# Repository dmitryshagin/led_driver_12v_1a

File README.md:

***WARNING! IT'S UNTESTED - I'VE NEVER BUILT THIS BOARD. But I will :)***

LED driver for powering Cree XHP35 LED at 1.05A from 3S LiPoly battery to use in underwater flashlight.

It's currently tuned up to work with 9-12.6V input.

Input can be easily changed to 4-25V with slight adjustment of R2 and R3. Increasing voltage over 25V is limited by used capacitors and FETs. You can change it upto ~60V with selecting new Q1-Q5, but PCB rework is also required.

Current is roughly set to 2A with R11, and is fine-tuned to 1.048A with R14&R15. Tuning R14 and R15 values makes it possible to set any current between 0-2A.

This driver is build around [LT3791](http://www.linear.com/product/LT3791)

I've also added Attiny24 to control PWM input and monitor input voltage. It can be ignored and never placed. Firmware will be added later, but the idea is to detect power loss with Q6, go to deep sleep and change working mode on power recovery. C16 gives uC ~4 seconds of life in power down mode, so we can switch power modes with one romote switch. Simulation gave me 10us for uC to go to deep sleep mode and it seems perfect.

You can download [gerbers](binaries/led_driver_12v_1a.zip?raw=true) to order this PCB from [SeedStudio](http://www.seeedstudio.com/service/index.php?r=pcb) - it's very cheap and has nice quality.

[BOM](https://www.digikey.com/classic/RegisteredUser/BOMBillOfMaterials.aspx?path=1&exist=1&id=3307608) - only for registered DigiKey users. Total cost is nearly $27 now.

Yo'll get something like this:

Board is 19.5x35mm and it should generate almost no heat - calculated efficiency is >96.5% and power loss is around 0.4W at 13W output.

It's also round version (32mm):

[Part List](part_list.txt?raw=true) is also included.

You can also take a look at LTSpice IV simulation and efficiency report. Schematic and PCB created with [Eagle 7.5](http://www.cadsoftusa.com/). It's not as nice and clean as I wanted it to be, but it should do the job.

**Changes required to use XHP70:**

It is very easy to modify this driver for XHP70 LED (12V version, at 2.4A). Modifications are simple:

* change R11 to 0.033 Ohm (sized 1206, power rating - 0.5 to 1W). Something like Panasonic ERJ-8BWFR033V. It will limit driver output current to 3A
* change R15 to 100k (0402 size) to fine-tune output current at 2.4A.
* change L1 to 10uH with sauration current at least 4A. Wurth Electronics 7447709100 will fit perfectly
* you can also remove L2 to boost efficiency to >98%, but it requires good wireing and low battery impedance (input current will pulse between 2.7 and 3.5Amps (with spikes to 10-15Amps) for 0.01 Ohm battery impedance). Instead we loose ~0.2W at L2, but have no power pulsation on input (<0.04A & stable input current 3.2A).

LTSpice simulation results:

* input power: 36.3W @ 11.7V
* output power: 35.5W @ 2.42A
* calculated efficiency: 97.8%
* LED current pulses: <1.7%

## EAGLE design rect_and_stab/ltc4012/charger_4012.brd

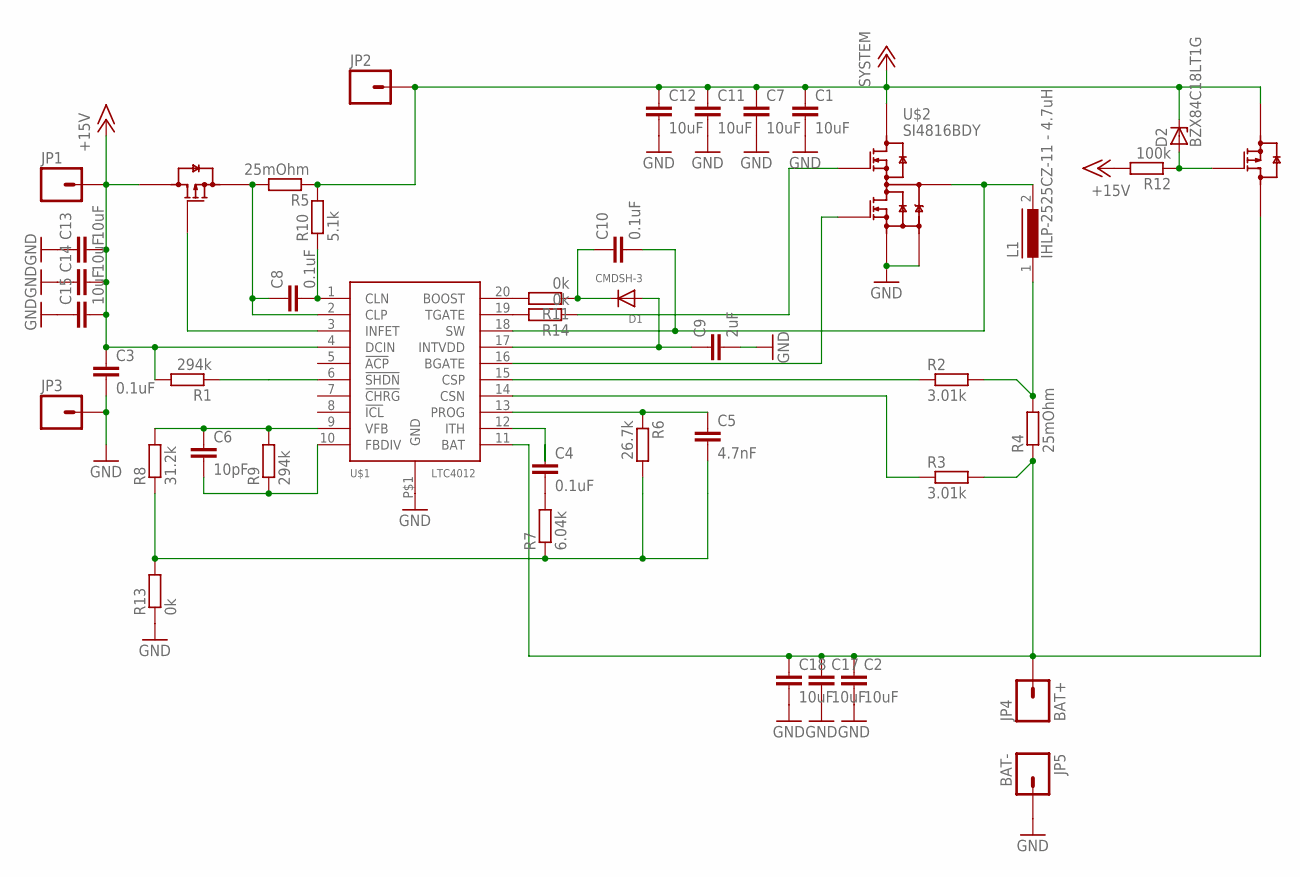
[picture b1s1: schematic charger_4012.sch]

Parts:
C1, C2, C7, C11, C12, C13, C14, C15, C17, C18: 10uF; C1206
C3, C4, C8, C10: 0.1uF; C0402
C5: 4.7nF; C0402
C6: 10pF; C0402
C9: 2uF; C0805
D1: CMDSH-3; SOD-323F
D2: BZX84C18LT1G; TO236
JP1, JP2, JP3: M01PTH_2MM; 1X01_2MM
JP4: BAT+; 1X01_2MM
JP5: BAT-; 1X01_2MM
L1: IHLP-2525CZ-11 - 4.7uH; DR73
R1, R9: 294k; R0402
R2, R3: 3.01k; R0402
R4, R5: 25mOhm; R2512
R6: 26.7k; R0402
R7: 6.04k; R0402
R8: 31.2k; R0402
R10: 5.1k; R0402
R11, R13, R14: 0k; R0402
R12: 100k; R0402
U$1: LTC4012; QFN20
U$2: SI4816BDY; SO-8
U$3, U$4: SI7423DN; POWERPACK1212

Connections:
+12V: C1.1, C7.1, C11.1, C12.1, D2.C, JP2.1, R5.1, R10.2, U$2.8 (D1), U$4.1 (S), U$4.2 (S), U$4.3 (S)
+15V: C3.1, C13.2, C14.2, C15.2, JP1.1, R1.2, R12.2, U$1.4 (DCIN), U$3.5 (D), U$3.6 (D), U$3.7 (D), U$3.8 (D), U$3.9 (D)
BAT: C2.1, C17.1, C18.1, JP4.1, R3.2, R4.1, U$1.11 (BAT), U$4.5 (D), U$4.6 (D), U$4.7 (D), U$4.8 (D), U$4.9 (D)
BGATE: U$1.16 (BGATE), U$2.4 (G2)
BOOST: C10.1, D1.C, R11.1
CLN: C8.2, R10.1, U$1.1 (CLN)
CSN: R3.1, U$1.14 (CSN)
CSP: R2.1, U$1.15 (CSP)
FBDIV: C6.2, R9.1, U$1.10 (FBDIV)
GND: C1.2, C2.2, C3.2, C7.2, C9.2, C11.2, C12.2, C13.1, C14.1, C15.1, C17.2, C18.2, JP3.1, JP5.1, R13.1, U$1.P$1 (GND), U$2.2 (A), U$2.3 (S2)
INFET: U$1.3 (INFET), U$3.4 (G)
INTVDD: C9.1, D1.A, U$1.17 (INTVDD)
ITH: C4.1, U$1.12 (ITH)
unnamed: R14.2, U$1.19 (TGATE)
unnamed: L1.1, R2.2, R4.2
unnamed: C4.2, R7.2
unnamed: R1.1, U$1.6 (!SHDN)
unnamed: C8.1, R5.2, U$1.2 (CLP), U$3.1 (S), U$3.2 (S), U$3.3 (S)
unnamed: R11.2, U$1.20 (BOOST)
unnamed: D2.A, R12.1, U$4.4 (G)
PROG: C5.1, R6.1, U$1.13 (PROG)
SGND: C5.2, R6.2, R7.1, R8.1, R13.2
SW: C10.2, L1.2, U$1.18 (SW), U$2.5 (S1/D2), U$2.6 (S1/D2), U$2.7 (S1/D2)
TGATE: R14.1, U$2.1 (G1)
VFB: C6.1, R8.2, R9.2, U$1.9 (VFB)

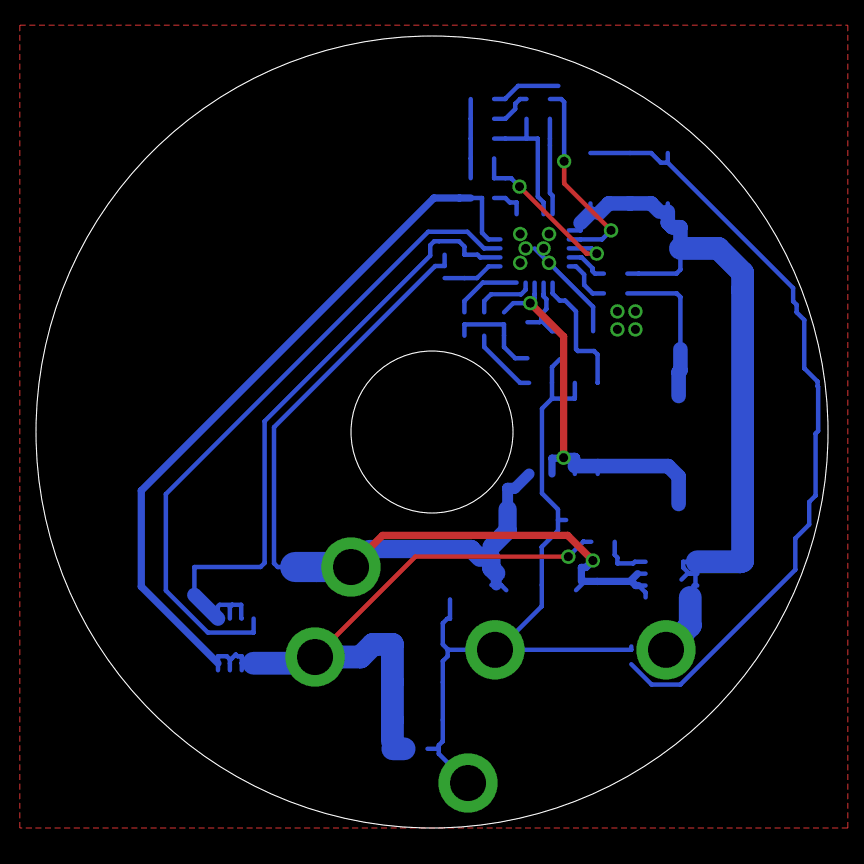
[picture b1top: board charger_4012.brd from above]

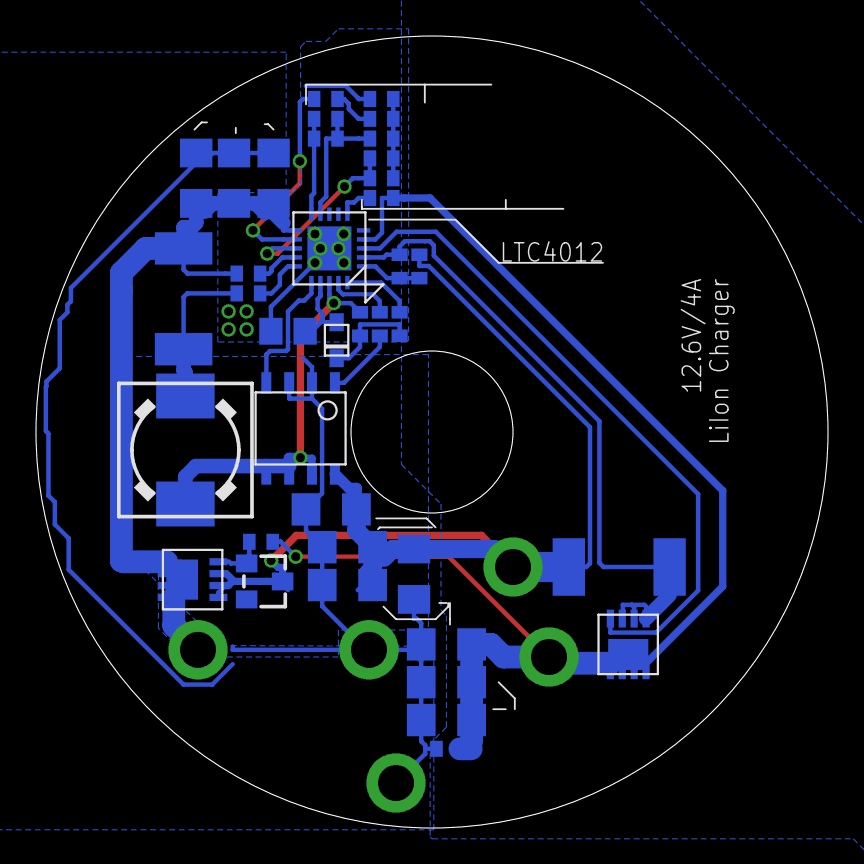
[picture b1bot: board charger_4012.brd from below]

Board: 2 copper layers, 44.0 x 44.0 mm, 43 parts (38 on the bottom side), 25 nets.

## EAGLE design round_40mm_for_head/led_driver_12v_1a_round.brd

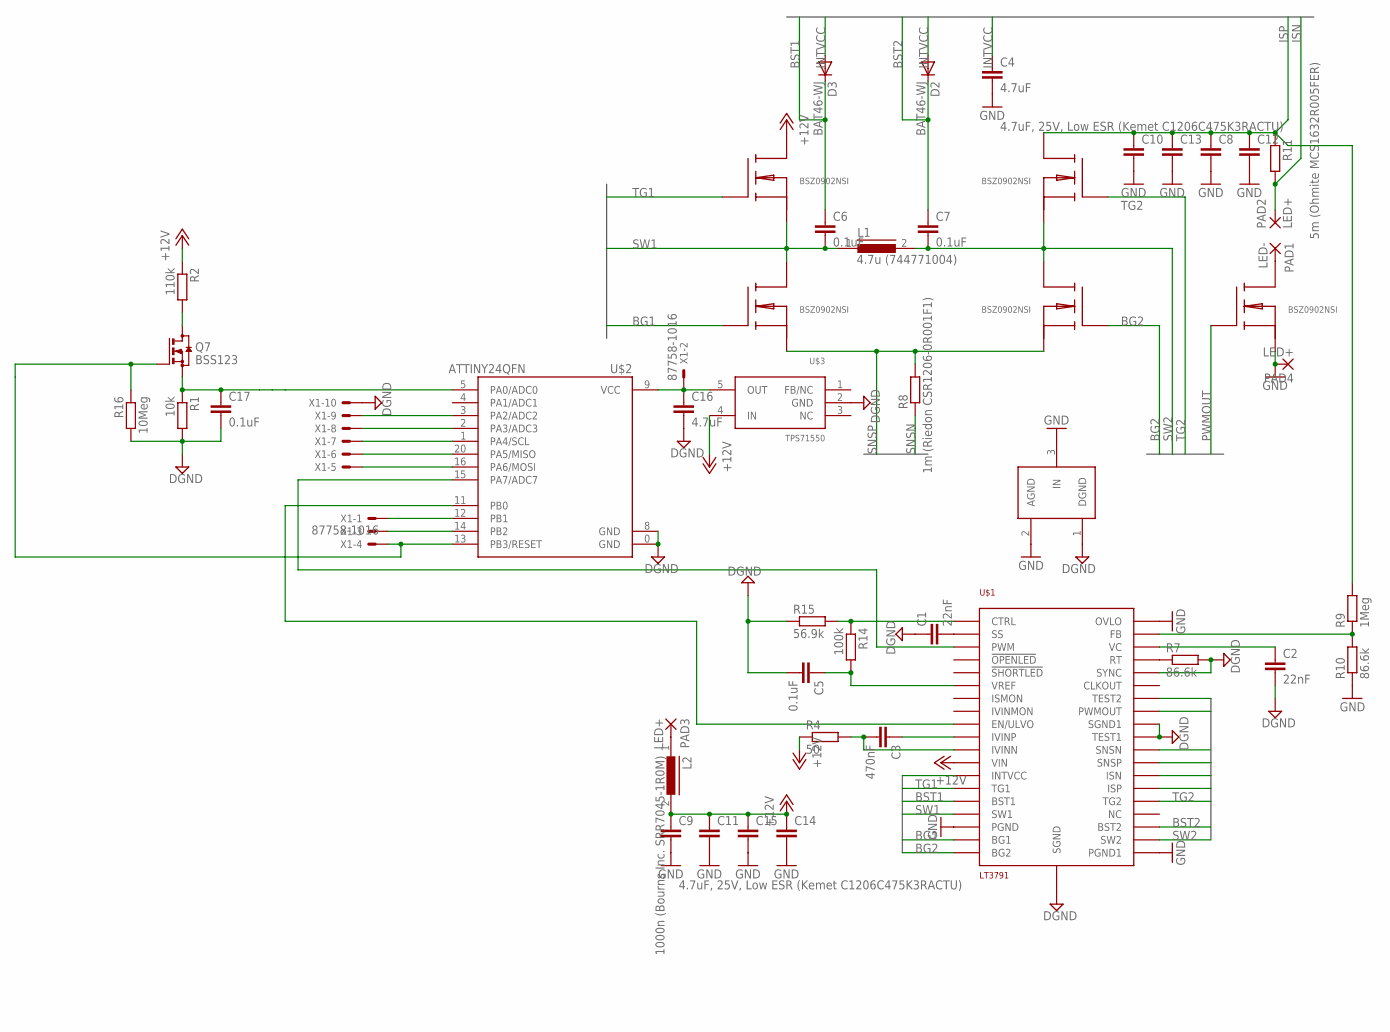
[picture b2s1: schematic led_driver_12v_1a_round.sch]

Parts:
C1: 22nF; C0402
C2: 22nF; C0402K
C3: 470nF; C0402K
C4, C16: 4.7uF; C1206
C5, C6, C7, C17: 0.1uF; C0402K
C8, C9, C10, C11, C12, C13, C14, C15: 4.7uF, 25V, Low ESR (Kemet C1206C475K3RACTU); C1206
D2, D3: BAT46-WJ; SOD323-W
L1: 4.7u (744771004); DR127
L2: 1000n (Bourns Inc. SRR7045-1R0M); DR74
PAD1: LED-; 3,81/1,4
PAD2: LED+; 3,81/1,4
PAD3, PAD4: LED+; 5-2,5
Q1, Q2, Q3, Q4, Q5: BSZ0902NSI; BSZ090X
Q7: BSS123; SOT23
R1: 10k; R0402
R2: 110k; R0402
R4: 50; R0402
R7, R10: 86.6k; R0402
R8: 1m (Riedon CSR1206-0R001F1); R1206
R9: 1Meg; R0402
R11: 5m (Ohmite MCS1632R005FER); R1206
R14: 100k; R0402
R15: 56.9k; R0402
R16: 10Meg; R0402
U$1: LT3791; TSSOP38
U$2: ATTINY24QFN; QFN20
U$3: TPS71550; SC70
U$4: GND_CONNECT
X1: 87758-1016

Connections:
+12V: C9.1, C11.1, C14.1, C15.1, L2.2, Q1.D, Q1.D@1 (D), Q1.D@2 (D), Q1.D@3 (D), Q1.D@4 (D), R2.1, R4.1, U$1.P$12 (VIN), U$3.4 (IN)
BG1: Q2.G, U$1.P$18 (BG1)
BG2: Q3.G, U$1.P$19 (BG2)
BST1: C6.1, D3.C, U$1.P$15 (BST1)
BST2: C7.1, D2.C, U$1.P$22 (BST2)
DGND: C1.1, C2.2, C5.2, C16.2, C17.2, R1.2, R7.2, R15.1, R16.2, U$1.P$29 (TEST1), U$1.P$30 (SGND), U$1.P$34 (SYNC), U$1.P$39 (SGND1), U$2.0 (GND), U$2.8 (GND), U$3.2 (GND), U$4.1 (DGND), X1.10
GND: C4.2, C8.2, C9.2, C10.2, C11.2, C12.2, C13.2, C14.2, C15.2, PAD4.1, Q5.S@1 (S), Q5.S@2 (S), Q5.S@3 (S), Q5.S@4 (S), R10.1, U$1.P$17 (PGND), U$1.P$20 (PGND1), U$1.P$38 (OVLO), U$4.2 (AGND), U$4.3 (IN)
INTVCC: C4.1, D2.A, D3.A, U$1.P$13 (INTVCC), U$1.P$32 (TEST2)
ISN: PAD2.1, R11.2, U$1.P$26 (ISN)
ISP: C8.1, C10.1, C12.1, C13.1, Q4.D, Q4.D@1 (D), Q4.D@2 (D), Q4.D@3 (D), Q4.D@4 (D), R9.2, R11.1, U$1.P$25 (ISP)
MISO: U$2.20 (PA5/MISO), X1.6
MOSI: U$2.16 (PA6/MOSI), X1.5
unnamed: C5.1, R14.2, U$1.P$6 (VREF)
unnamed: R14.1, R15.2, U$1.P$1 (CTRL)
unnamed: R7.1, U$1.P$35 (RT)
unnamed: C1.2, U$1.P$2 (SS)
unnamed: C2.1, U$1.P$36 (VC)
unnamed: R9.1, R10.2, U$1.P$37 (FB)
unnamed: C3.1, U$1.P$10 (IVINP)
unnamed: Q7.3 (D), R2.2
unnamed: C3.2, R4.2, U$1.P$11 (IVINN)
unnamed: U$1.P$9 (EN/ULVO), U$2.11 (PB0)
unnamed: C16.1, U$2.9 (VCC), U$3.5 (OUT), X1.2
unnamed: U$1.P$3 (PWM), U$2.15 (PA7/ADC7)
unnamed: C17.1, Q7.2 (S), R1.1, U$2.5 (PA0/ADC0)
unnamed: PAD1.1, Q5.D, Q5.D@1 (D), Q5.D@2 (D), Q5.D@3 (D), Q5.D@4 (D)
unnamed: L2.1, PAD3.1
PA2: U$2.3 (PA2/ADC2), X1.9
PA3: U$2.2 (PA3/ADC3), X1.8
PB1: U$2.12 (PB1), X1.1
PB2: U$2.14 (PB2), X1.3
PWMOUT: Q5.G, U$1.P$31 (PWMOUT)
RESET: Q7.1 (G), R16.1, U$2.13 (PB3/RESET), X1.4
SCL: U$2.1 (PA4/SCL), X1.7
SNSN: R8.1, U$1.P$28 (SNSN)
SNSP: Q2.S@1 (S), Q2.S@2 (S), Q2.S@3 (S), Q2.S@4 (S), Q3.S@1 (S), Q3.S@2 (S), Q3.S@3 (S), Q3.S@4 (S), R8.2, U$1.P$27 (SNSP)
SW1: C6.2, L1.1, Q1.S@1 (S), Q1.S@2 (S), Q1.S@3 (S), Q1.S@4 (S), Q2.D, Q2.D@1 (D), Q2.D@2 (D), Q2.D@3 (D), Q2.D@4 (D), U$1.P$16 (SW1)
SW2: C7.2, L1.2, Q3.D, Q3.D@1 (D), Q3.D@2 (D), Q3.D@3 (D), Q3.D@4 (D), Q4.S@1 (S), Q4.S@2 (S), Q4.S@3 (S), Q4.S@4 (S), U$1.P$21 (SW2)
TG1: Q1.G, U$1.P$14 (TG1)
TG2: Q4.G, U$1.P$24 (TG2)

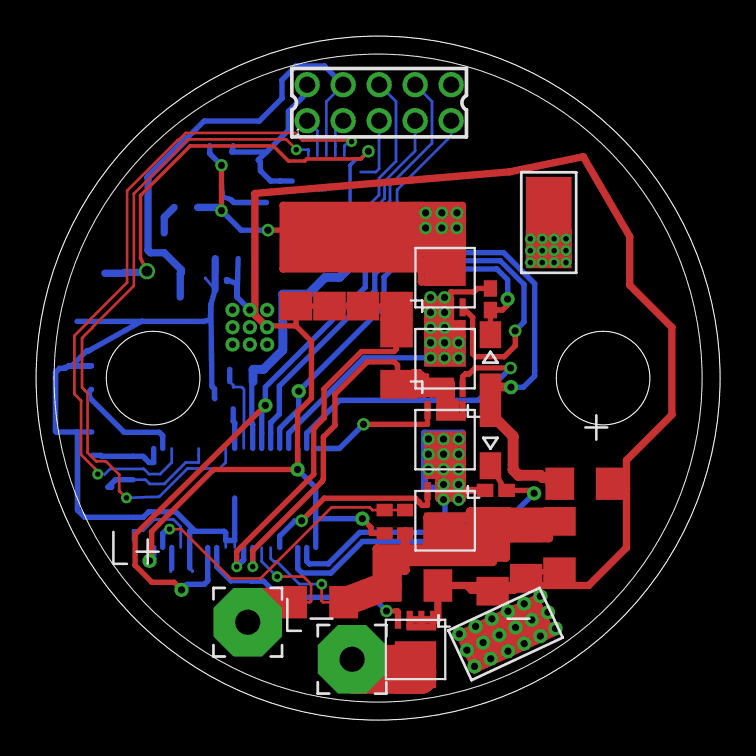
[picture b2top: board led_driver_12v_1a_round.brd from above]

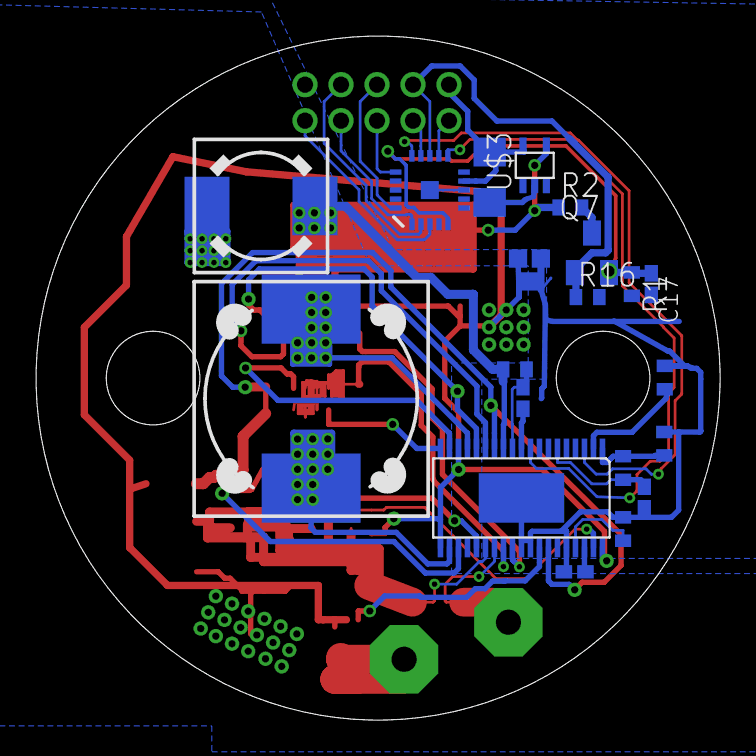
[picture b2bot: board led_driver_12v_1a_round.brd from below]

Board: 2 copper layers, 38.0 x 38.0 mm, 47 parts (20 on the bottom side), 40 nets.

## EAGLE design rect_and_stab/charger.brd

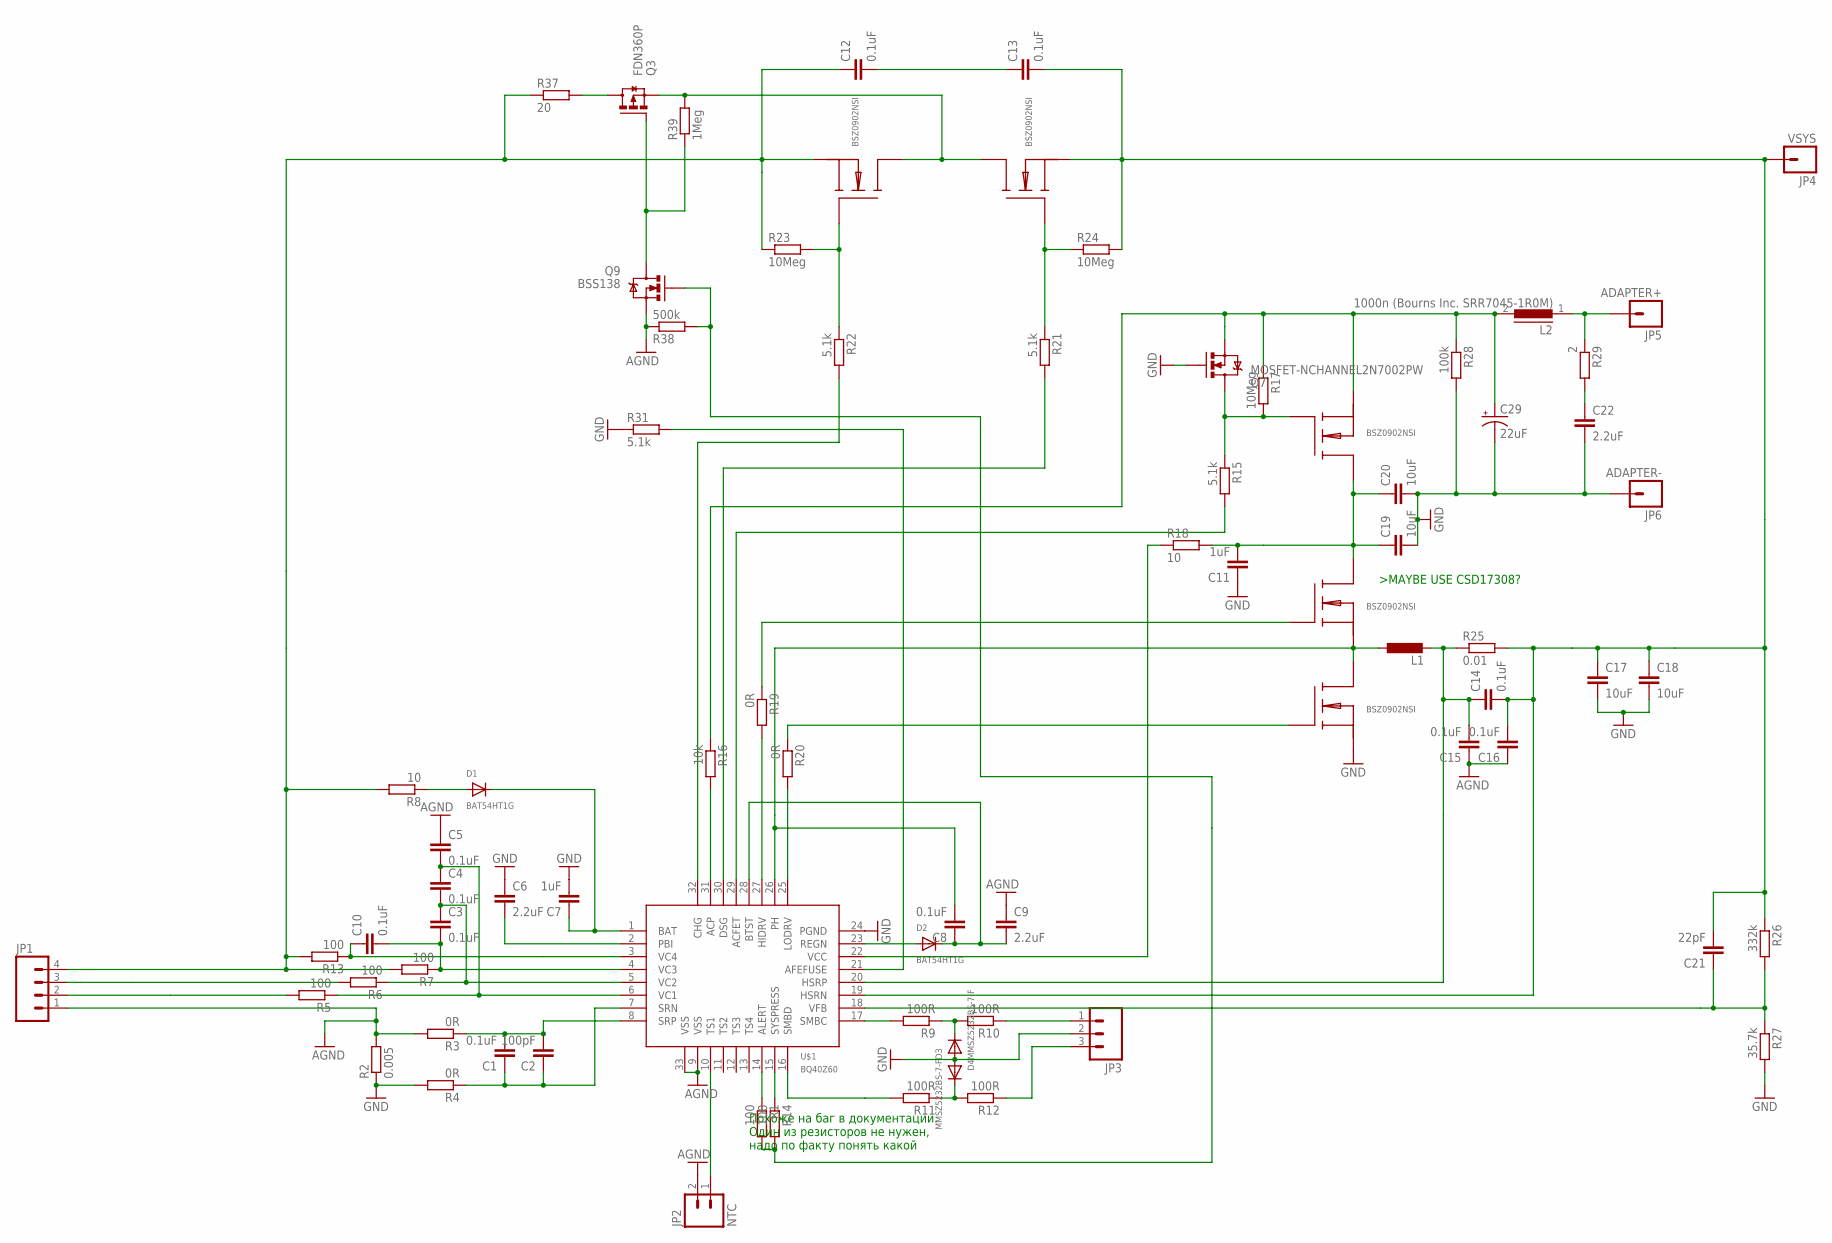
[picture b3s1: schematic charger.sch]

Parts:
C1, C3, C4, C5, C8, C10, C12, C13, C14, C15, C16: 0.1uF; C0402
C2: 100pF; C0402
C6, C9, C22: 2.2uF; C0805
C7: 1uF; C0603
C11: 1uF; C0805
C17, C18, C19, C20: 10uF; C1206
C21: 22pF; C0402
C29: 22uF; EIA7343
D1, D2: BAT54HT1G; SOD-323F
D3, D4: MMSZ5232BS-7-F; SOD-323F
JP1: M04PTH; 1X04
JP2: NTC; 1X02
JP3: M03PTH; 1X03
JP4: VSYS; 1X01_2MM
JP5: ADAPTER+; 1X01_2MM
JP6: ADAPTER-; 1X01_2MM
L1: L-EUL5650M; L5650M
L2: 1000n (Bourns Inc. SRR7045-1R0M); DR74
Q1, Q2, Q4, Q5, Q8: BSZ0902NSI; BSZ090X
Q3: FDN360P; SUPER-SOT3
Q7: MOSFET-NCHANNEL2N7002PW; SOT323
Q9: BSS138; SOT323
R1, R14: 100; R0402
R2: 0.005; R1210
R3, R4, R19, R20: 0R; R0402
R5, R6, R7, R13: 100; R0603
R8: 10; R0603
R9, R10, R11, R12: 100R; R0402
R15, R21, R22, R31: 5.1k; R0402
R16: 10k; R0402
R17, R23, R24: 10Meg; R0402
R18: 10; R1206
R25: 0.01; R2010
R26: 332k; R0402
R27: 35.7k; R0402
R28: 100k; R0402
R29: 2; R0603
R37: 20; R1210
R38: 500k; R0402
R39: 1Meg; R0402
U$1: BQ40Z60

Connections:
AGND: C5.1, C9.1, C15.1, C16.1, JP1.1, JP2.2, Q9.2 (S), R2.2, R3.2, R38.1, U$1.9 (VSS), U$1.33 (VSS)
GND: C6.1, C7.2, C11.1, C17.2, C18.2, C19.2, C20.2, C22.2, C29.C (-), D3.A, D4.A, JP3.2, JP6.1, Q2.S@1 (S), Q2.S@2 (S), Q2.S@3 (S), Q2.S@4 (S), Q7.1 (G), R2.1, R4.2, R27.2, R28.2, R31.1, U$1.24 (PGND)
unnamed: C1.2, C2.2, R3.1, U$1.8 (SRP)
unnamed: C1.1, C2.1, R4.1, U$1.7 (SRN)
unnamed: JP1.2, R5.2
unnamed: C7.1, D1.C, U$1.1 (BAT)
unnamed: C4.1, C5.2, R5.1, U$1.6 (VC1)
unnamed: C3.2, C10.2, R7.1, U$1.4 (VC3)
unnamed: JP1.4, R7.2, R8.2, R13.2
unnamed: JP1.3, R6.2
unnamed: C3.1, C4.2, R6.1, U$1.5 (VC2)
unnamed: C6.2, U$1.2 (PBI)
unnamed: D1.A, R8.1
unnamed: JP2.1, U$1.10 (TS1)
unnamed: R1.1, U$1.14 (ALERT)
unnamed: R9.2, U$1.17 (SMBC)
unnamed: R11.2, U$1.16 (SMBD)
unnamed: C10.1, R13.1, U$1.3 (VC4)
unnamed: D4.C, R11.1, R12.2
unnamed: D3.C, R9.1, R10.2
unnamed: JP3.1, R10.1
unnamed: C22.1, R29.2
unnamed: Q3.2 (S), Q4.D, Q4.D@1 (D), Q4.D@2 (D), Q4.D@3 (D), Q4.D@4 (D), Q5.D, Q5.D@1 (D), Q5.D@2 (D), Q5.D@3 (D), Q5.D@4 (D), R39.2
unnamed: JP3.3, R12.1
unnamed: D2.A, U$1.23 (REGN)
unnamed: C8.1, C9.2, D2.C, U$1.28 (BTST)
unnamed: R31.2, U$1.21 (AFEFUSE)
unnamed: C12.1, Q4.S@1 (S), Q4.S@2 (S), Q4.S@3 (S), Q4.S@4 (S), R23.1, R37.1
unnamed: C11.2, C19.1, C20.1, Q1.D, Q1.D@1 (D), Q1.D@2 (D), Q1.D@3 (D), Q1.D@4 (D), Q8.D, Q8.D@1 (D), Q8.D@2 (D), Q8.D@3 (D), Q8.D@4 (D), R18.2
unnamed: C8.2, L1.1, Q1.S@1 (S), Q1.S@2 (S), Q1.S@3 (S), Q1.S@4 (S), Q2.D, Q2.D@1 (D), Q2.D@2 (D), Q2.D@3 (D), Q2.D@4 (D), U$1.26 (PH)
unnamed: Q7.3 (D), Q8.G, R15.1, R17.2
unnamed: R15.2, U$1.29 (ACFET)
unnamed: R16.2, U$1.31 (ACP)
unnamed: R18.1, U$1.22 (VCC)
unnamed: C21.1, R26.2, R27.1, U$1.18 (VFB)
unnamed: R19.2, U$1.27 (HIDRV)
unnamed: R20.2, U$1.25 (LODRV)
unnamed: Q1.G, R19.1
unnamed: Q2.G, R20.1
unnamed: R21.2, U$1.30 (DSG)
unnamed: Q5.G, R21.1, R24.1
unnamed: R22.2, U$1.32 (CHG)
unnamed: Q4.G, R22.1, R23.2
unnamed: C12.2, C13.1
unnamed: C14.1, C15.2, L1.2, R25.1, U$1.20 (HSRP)
unnamed: C13.2, C14.2, C16.2, C17.1, C18.1, C21.2, JP4.1, Q5.S@1 (S), Q5.S@2 (S), Q5.S@3 (S), Q5.S@4 (S), R24.2, R25.2, R26.1, U$1.19 (HSRN)
unnamed: Q3.3 (D), R37.2
unnamed: Q9.1 (G), R1.2, R14.2, R38.2
unnamed: Q3.1 (G), Q9.3 (D), R39.1
unnamed: R14.1, U$1.15 (SYSPRESS)
unnamed: C29.A (+), L2.2, Q7.2 (S), Q8.S@1 (S), Q8.S@2 (S), Q8.S@3 (S), Q8.S@4 (S), R16.1, R17.1, R28.1
unnamed: JP5.1, L2.1, R29.1

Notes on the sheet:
Похоже на баг в документации. Один из резисторов не нужен, надо по факту понять какой

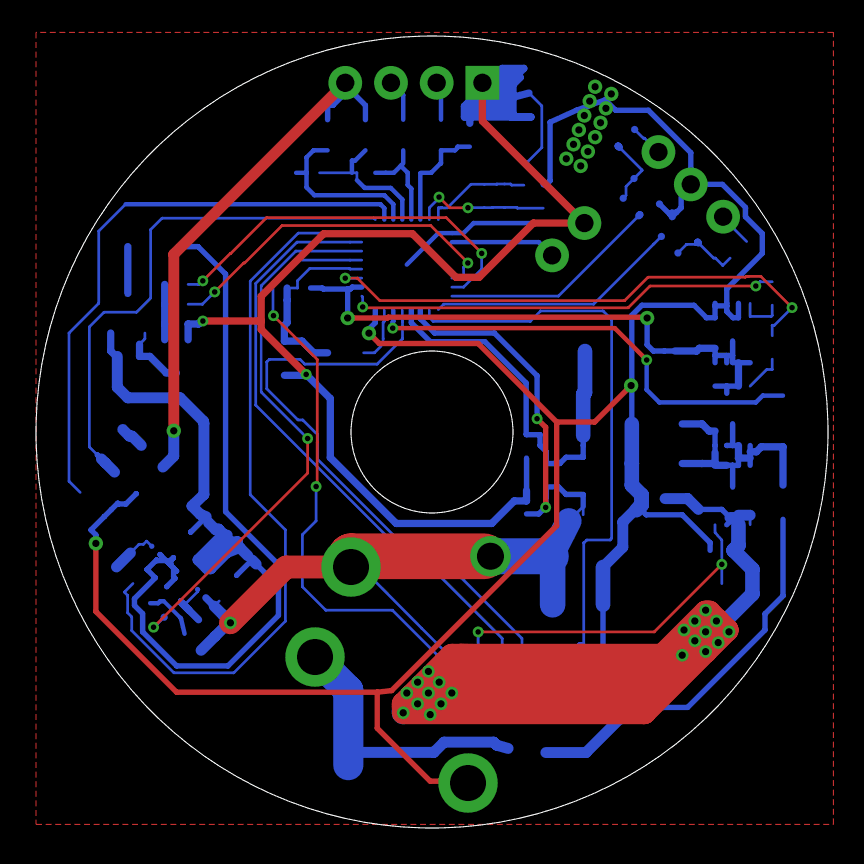
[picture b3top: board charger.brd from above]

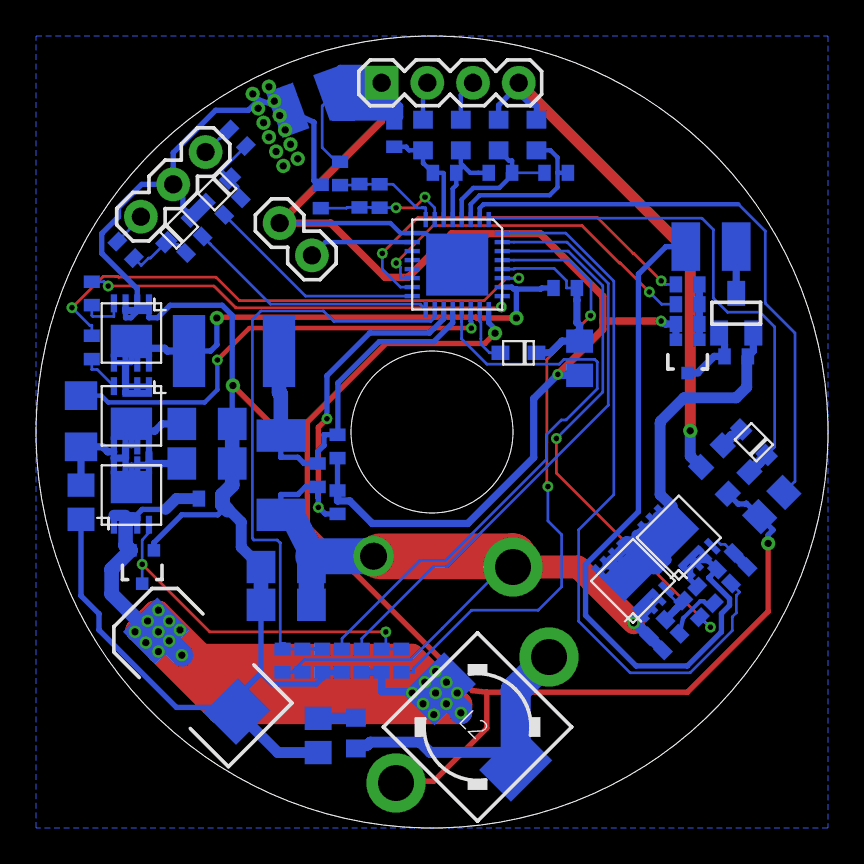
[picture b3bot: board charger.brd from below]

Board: 2 copper layers, 44.0 x 44.0 mm, 77 parts (74 on the bottom side), 52 nets.

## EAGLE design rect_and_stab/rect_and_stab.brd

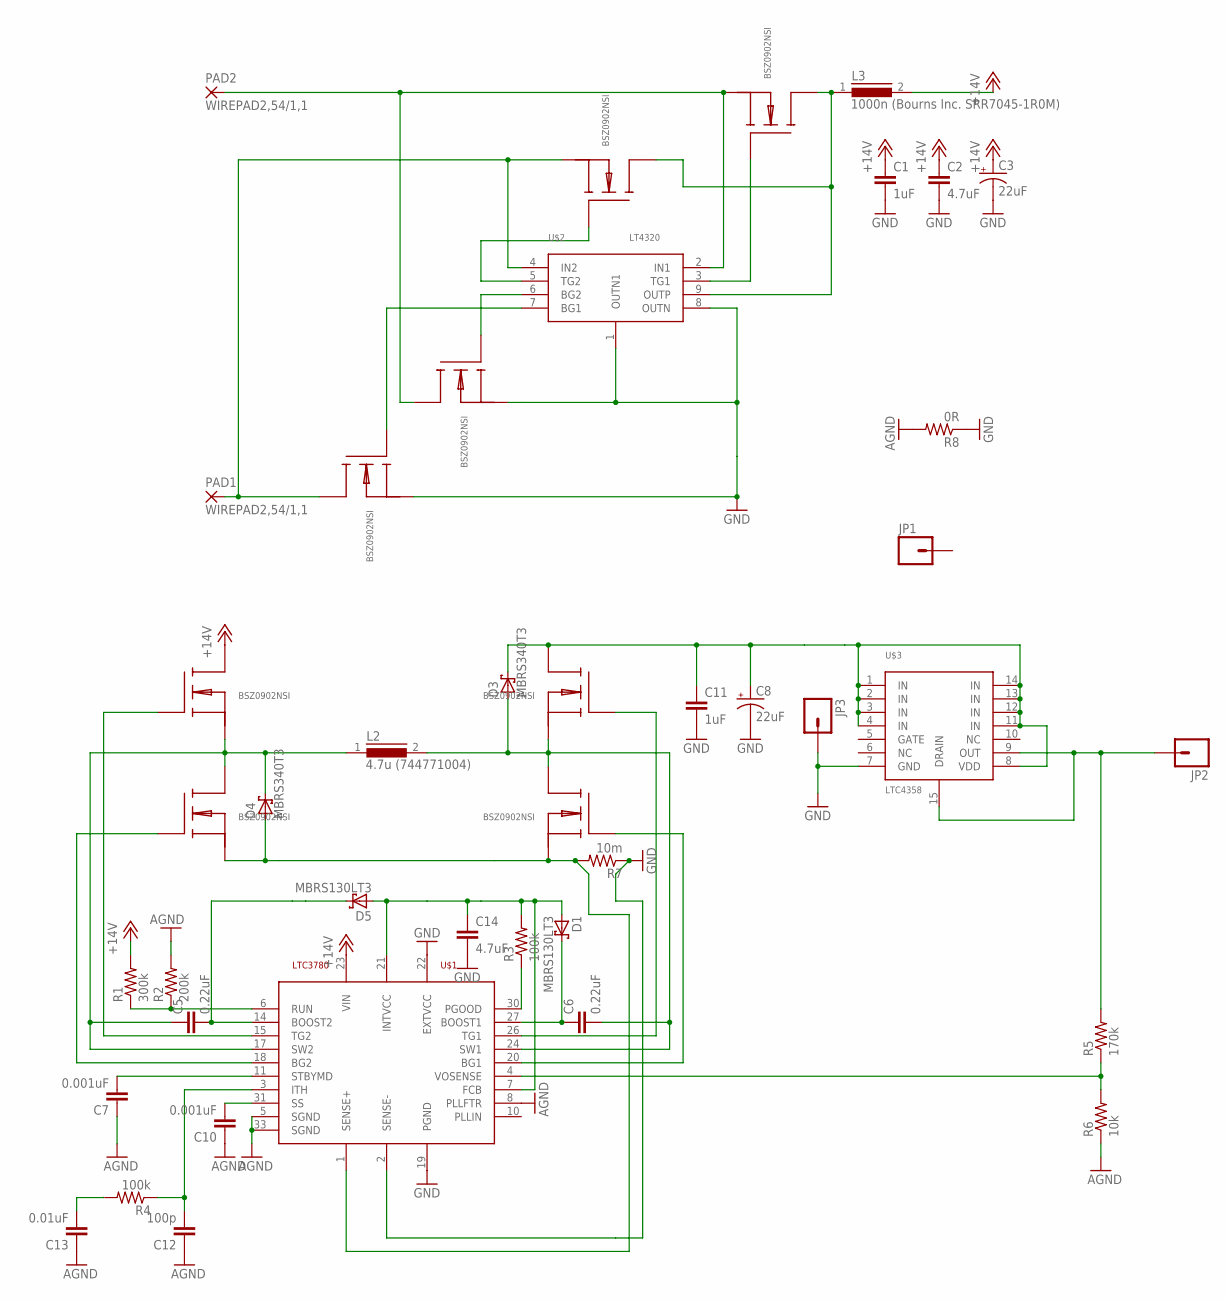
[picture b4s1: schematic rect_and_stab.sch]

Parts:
C1, C11: 1uF; 0603-CAP
C2, C14: 4.7uF; 1210
C3, C8: 22uF; EIA7343
C5, C6: 0.22uF; 0603-CAP
C7, C10: 0.001uF; 0402-CAP
C12: 100p; 0402-CAP
C13: 0.01uF; 0402-CAP
D1, D5: MBRS130LT3; SMB
D3, D4: MBRS340T3; SMC
JP1, JP2, JP3: M01PTH_2MM; 1X01_2MM
L2: 4.7u (744771004); DR127
L3: 1000n (Bourns Inc. SRR7045-1R0M); DR74
PAD1, PAD2: WIREPAD2,54/1,1; 2,54/1,1
Q1, Q2, Q3, Q4, Q5, Q6, Q7, Q8: BSZ0902NSI; BSZ090X
R1: 300k; 0402-RES
R2: 200k; 0402-RES
R3, R4: 100k; 0402-RES
R5: 170k; 0402-RES
R6: 10k; 0402-RES
R7: 10m; R2010
R8: 0R; 0402-RES
U$1: LTC3780
U$2: LT4320
U$3: LTC4358

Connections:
+12V: C1.1, C2.1, C3.A (+), L3.2, Q6.D, Q6.D@1 (D), Q6.D@2 (D), Q6.D@3 (D), Q6.D@4 (D), R1.2, U$1.23 (VIN)
AGND: C7.1, C10.1, C12.1, C13.1, R2.2, R6.1, R8.2, U$1.5 (SGND), U$1.8 (PLLFTR), U$1.33 (SGND)
GND: C1.2, C2.2, C3.C (-), C8.C (-), C11.2, C14.2, JP3.1, Q1.S@1 (S), Q1.S@2 (S), Q1.S@3 (S), Q1.S@4 (S), Q3.S@1 (S), Q3.S@2 (S), Q3.S@3 (S), Q3.S@4 (S), R7.1, R8.1, U$1.2 (SENSE-), U$1.19 (PGND), U$1.22 (EXTVCC), U$2.1 (OUTN1), U$2.8 (OUTN), U$3.7 (GND)
unnamed: Q2.G, U$2.5 (TG2)
unnamed: PAD1.1, Q2.S@1 (S), Q2.S@2 (S), Q2.S@3 (S), Q2.S@4 (S), Q3.D, Q3.D@1 (D), Q3.D@2 (D), Q3.D@3 (D), Q3.D@4 (D), U$2.4 (IN2)
unnamed: Q3.G, U$2.7 (BG1)
unnamed: C7.2, U$1.11 (STBYMD)
unnamed: C6.1, D1.C, U$1.27 (BOOST1)
unnamed: Q1.G, U$2.6 (BG2)
unnamed: PAD2.1, Q1.D, Q1.D@1 (D), Q1.D@2 (D), Q1.D@3 (D), Q1.D@4 (D), Q4.S@1 (S), Q4.S@2 (S), Q4.S@3 (S), Q4.S@4 (S), U$2.2 (IN1)
unnamed: Q4.G, U$2.3 (TG1)
unnamed: L3.1, Q2.D, Q2.D@1 (D), Q2.D@2 (D), Q2.D@3 (D), Q2.D@4 (D), Q4.D, Q4.D@1 (D), Q4.D@2 (D), Q4.D@3 (D), Q4.D@4 (D), U$2.9 (OUTP)
unnamed: Q7.G, U$1.20 (BG1)
unnamed: C6.2, D3.A, L2.2, Q7.D, Q7.D@1 (D), Q7.D@2 (D), Q7.D@3 (D), Q7.D@4 (D), Q8.S@1 (S), Q8.S@2 (S), Q8.S@3 (S), Q8.S@4 (S), U$1.24 (SW1)
unnamed: C10.2, U$1.31 (SS)
unnamed: JP2.1, R5.2, U$3.9 (OUT), U$3.15 (DRAIN)
unnamed: Q8.G, U$1.26 (TG1)
unnamed: Q5.G, U$1.18 (BG2)
unnamed: C5.1, D4.C, L2.1, Q5.D, Q5.D@1 (D), Q5.D@2 (D), Q5.D@3 (D), Q5.D@4 (D), Q6.S@1 (S), Q6.S@2 (S), Q6.S@3 (S), Q6.S@4 (S), U$1.17 (SW2)
unnamed: Q6.G, U$1.15 (TG2)
unnamed: C5.2, D5.C, U$1.14 (BOOST2)
unnamed: R5.1, R6.2, U$1.4 (VOSENSE)
unnamed: R1.1, R2.1, U$1.6 (RUN)
unnamed: R3.1, U$1.30 (PGOOD)
unnamed: C8.A (+), C11.1, D3.C, Q8.D, Q8.D@1 (D), Q8.D@2 (D), Q8.D@3 (D), Q8.D@4 (D), U$3.1 (IN), U$3.2 (IN), U$3.3 (IN), U$3.4 (IN), U$3.8 (VDD), U$3.11 (IN), U$3.12 (IN), U$3.13 (IN), U$3.14 (IN)
unnamed: D4.A, Q5.S@1 (S), Q5.S@2 (S), Q5.S@3 (S), Q5.S@4 (S), Q7.S@1 (S), Q7.S@2 (S), Q7.S@3 (S), Q7.S@4 (S), R7.2, U$1.1 (SENSE+)
unnamed: C13.2, R4.2
unnamed: C12.2, R4.1, U$1.3 (ITH)
unnamed: C14.1, D1.A, D5.A, R3.2, U$1.7 (FCB), U$1.21 (INTVCC)

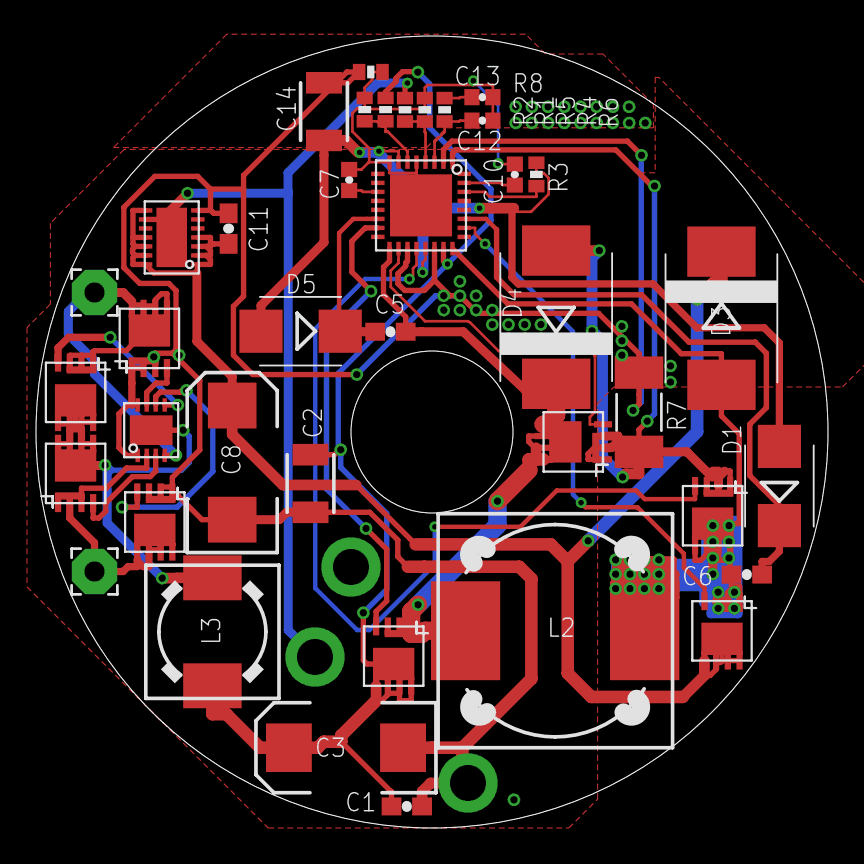
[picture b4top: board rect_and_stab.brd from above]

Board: 2 copper layers, 44.0 x 44.0 mm, 42 parts (0 on the bottom side), 29 nets.

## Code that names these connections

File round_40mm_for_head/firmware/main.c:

#include <avr/io.h>
#include <avr/delay.h>
#include <avr/interrupt.h>
#include <avr/sleep.h>
#include <avr/eeprom.h>
#include <string.h>

#define MODE_OFF			0
#define MODE_IDLE			1
#define MODE_OVERTEMP		2
#define MODE_LOW_VOLTAGE	3
#define MODE_LOW			4
#define MODE_HALF			5
#define MODE_FULL			6


#define LIMIT_9V  714
#define LIMIT_10V 793
#define LIMIT_11V 872
#define LIMIT_12V 951

#define BLUE_OFF 			(PORTA |=  (1<<PA4))
#define BLUE_ON 			(PORTA &= ~(1<<PA4))
#define GREEN_OFF 			(PORTA |=  (1<<PA3))
#define GREEN_ON 			(PORTA &= ~(1<<PA3))
#define RED_OFF  			(PORTA |=  (1<<PA2))
#define RED_ON  			(PORTA &= ~(1<<PA2))

#define LEFT_PRESSED 		(!(PINB & (1 << PB1)))
#define RIGHT_PRESSED 		(!(PINB & (1 << PB2)))

#define DRIVER_ON  			(PORTB |=  (1<<PB0))
#define DRIVER_OFF 			(PORTB &= ~(1<<PB0))


volatile uint8_t power_mode, prev_power_mode, unlock_stage, d_seconds, adc_channel, vals_pos=0;
volatile uint16_t vals[4];
volatile uint32_t val;
volatile uint32_t seconds;

uint32_t nv_seconds_on[] EEMEM = {0,0,0,0,0,0,0};
uint16_t nv_times_on[]   EEMEM = {0,0,0,0,0,0,0};
uint16_t nv_max_on[]     EEMEM = {0,0,0,0,0,0,0};

uint8_t times_occured[6];
const uint8_t zero_vals[6] = {0,0,0,0,0,0};

uint8_t led_selected, old_led_selected = 0;

uint32_t seconds_on[7];
uint16_t times_on[7];
uint16_t max_on[7];

ISR(ADC_vect){
	uint8_t theLowADC = ADCL;
	val = ADCH<<8 | theLowADC;
	ADCSRA |= 1<<ADSC;	//start conversion
}

ISR(PCINT1_vect){
	read_button();
}

ISR(TIM1_OVF_vect){
	d_seconds+=1;
	if(d_seconds==10){
		seconds+=1;
		d_seconds=0;
	}
	TCNT1 = 53035; //~=10Hz
}


void all_off(){
	stop_timer();
	unlock_stage = 0;
	seconds = 0;
	d_seconds = 0;
	apply_led(0);
	power_mode = MODE_OFF;
	apply_power();
	DRIVER_OFF;
	OCR0B=0;
	led_selected = 0;
	old_led_selected = 0;
	disable_adc();
	clean_times_occured();
}

void start_timer(){
	TCCR1A = 0;
	TCNT1 = 53035; 		 //~=10Hz
	TCCR1B = (1<<CS11);
	TIMSK1 = (1<<TOIE1); //timer1 interrupt enabled
	enable_adc();
	ADCSRA |= (1<<ADSC); //start ADC conversion
}

void stop_timer(){
	TIMSK1 = 0;
	TCCR1B = 0;
}

int apply_power(void){
	if(unlock_stage>0){
		RED_ON;
	}
	if(unlock_stage==3){ //unlock finished
		power_mode = MODE_IDLE;
		unlock_stage = 0;
	}
	if(power_mode==255){power_mode=MODE_IDLE;}
	if(power_mode>MODE_FULL){power_mode=MODE_FULL;}

	if(power_mode==MODE_OFF){
		DRIVER_OFF;
		OCR0B=0;
	}else{
		DRIVER_ON;
		set_sleep_mode(SLEEP_MODE_IDLE);
		sleep_disable();
		// stop_timer();
		start_timer();
	}
	// if(power_mode==MODE_IDLE)		{OCR0B=0;  }
	// if(power_mode==MODE_LOW_VOLTAGE){OCR0B=0; }
	// if(power_mode==MODE_OVERTEMP)	{OCR0B=0;  }
	// if(power_mode==MODE_LOW)		{OCR0B=16; }
	// if(power_mode==MODE_HALF)		{OCR0B=0;}
	// if(power_mode==MODE_FULL)		{OCR0B=0;}
	if(power_mode==MODE_IDLE)		{OCR0B=0;  }
	if(power_mode==MODE_LOW_VOLTAGE){OCR0B=16; }
	if(power_mode==MODE_OVERTEMP)	{OCR0B=8;  }
	if(power_mode==MODE_LOW)		{OCR0B=64; }
	if(power_mode==MODE_HALF)		{OCR0B=127;}
	if(power_mode==MODE_FULL)		{OCR0B=255;}

	if(prev_power_mode!=power_mode){
		seconds_on[prev_power_mode] += seconds;
		times_on[prev_power_mode] += 1;
		if(max_on[prev_power_mode] < seconds){
			max_on[prev_power_mode] = seconds;
		}
		if(power_mode==MODE_LOW_VOLTAGE||power_mode==MODE_OFF){
			//will store data only on power off or low batt to save eeprom
			eeprom_write_block(&seconds_on, &nv_seconds_on, sizeof(seconds_on));
			eeprom_write_block(&times_on,   &nv_times_on,   sizeof(times_on) );
			eeprom_write_block(&max_on,     &nv_max_on,     sizeof(max_on)   );
		}
		prev_power_mode=power_mode;
		seconds=0;
	}

	return 0;
}

void read_button(void){
	_delay_ms(200);
	uint32_t lock_timer=0;
	start_timer();
	if(LEFT_PRESSED){
		old_led_selected = led_selected;
		led_selected = 0;
		RED_OFF;GREEN_OFF;BLUE_ON;
		if(power_mode==MODE_OFF){
			if(unlock_stage==0 || unlock_stage==2){
				unlock_stage+=1;
				old_led_selected = 1;
			}
		}else{
			if(power_mode>MODE_LOW){
				power_mode-=1;
			}else{
				power_mode=1;
			}
		}
		apply_power();
		while(LEFT_PRESSED){lock_timer+=1;if(lock_timer==100000){all_off();}};
		apply_led(old_led_selected);
		_delay_ms(200);
		return;
	}
	if(RIGHT_PRESSED){
		old_led_selected = led_selected;
		led_selected = 0;
		RED_OFF;GREEN_OFF;BLUE_ON;
		if(power_mode==MODE_OFF){
			if(unlock_stage==1){
				unlock_stage+=1;
				old_led_selected = 1;
			}
		}else{
			if(power_mode>=MODE_LOW){ // проскакиваем аварийные режимы
				power_mode+=1;
			}else{
				power_mode=MODE_LOW;
			}
		}
		apply_power();
		while(RIGHT_PRESSED){};
		apply_led(old_led_selected);
		_delay_ms(200);
	}

}

void enable_adc(){
	ADCSRA = (1<<ADEN) | (1<<ADPS2) | (1<<ADPS1) | (1<<ADPS0) | (1<<ADIE);	// enable ADC on 1mhz/16 with interrupt
}

void disable_adc(){
	ADCSRA = 0;
}

void clean_times_occured(){
	memcpy(times_occured, zero_vals, sizeof(zero_vals));
}

int check_and_set_times(uint8_t idx){
	uint8_t prev = 0;
	prev = times_occured[idx];
	clean_times_occured();
	times_occured[idx]=prev+1;
	if(prev>4){
		clean_times_occured();
		return 1;
	}else{
		return 0;
	}
}

void apply_led(uint8_t led){
	if(led==0){
		RED_OFF;GREEN_OFF;BLUE_OFF;
	}
	if(led==1){
		RED_ON;GREEN_OFF;BLUE_OFF;
	}
	if(led==2){
		RED_OFF;GREEN_OFF;BLUE_ON;
	}
	if(led==3){
		RED_OFF;GREEN_ON;BLUE_OFF;
	}
}

int main(void){
	// PA0 - ADC IN
	// PA2 - RED
	// PA3 - GREEN
	// PA4 - BLUE
	// PA7(OC0B) - PWM output.
	// PB0 - out (EN)
	// PB1 - hall1, PB2 - hall2

	DDRA   = 0b11111110;
	PORTA  = 0b00000000;

	DDRB   = 0b0001;
	PORTB  = 0b0110;

	TCCR0A = (1 << COM0B1) | (1 << WGM00);// | (1 << WGM01);  		// PWM mode
	TCCR0B = (1 << CS01);							// clock source = CLK/8, start PWM

	PCMSK1 = (1<<PCINT9) | (1<<PCINT10);
	GIMSK = (1<<PCIE1);//interrupt on pin change0

	ADMUX = 0b10000000; // ADC0 - int

	apply_led(1);
	DRIVER_ON;
	OCR0B = 8;
	_delay_ms(500);
	all_off();

	eeprom_read_block(&seconds_on, &nv_seconds_on, sizeof(seconds_on));
	eeprom_read_block(&times_on,   &nv_times_on,   sizeof(times_on)  );
	eeprom_read_block(&max_on,     &nv_max_on,     sizeof(max_on)    );
	prev_power_mode = MODE_OFF;
	sei();

	while(1){
		// ADC8 = 330 - ~70 degrees Celcium
		// 9V =  714
		// 10V = 793
		// 11V = 872
		// 12V = 951
		// 12.6V = 999
		if(power_mode==MODE_OFF && unlock_stage==0){
			seconds = 0;
			d_seconds = 0;
			stop_timer();
			disable_adc();
			set_sleep_mode(SLEEP_MODE_PWR_DOWN);
			sleep_enable();
			sleep_bod_disable();
			sleep_cpu();
			sleep_disable();
		}
		if(seconds>1 && power_mode==MODE_OFF){
			all_off();
		}
		if(unlock_stage==0 && power_mode!=MODE_OFF){
			if(d_seconds==0){
				adc_channel = 0;
				ADMUX = 0b10000000; // ADC0 - int
			}
			if(d_seconds==5){
				adc_channel = 1;
				ADMUX = 0b10100010; // int reference and temp sensor
			}

			if(seconds%2==0){
				if(power_mode==MODE_LOW_VOLTAGE){
					RED_ON;GREEN_OFF;BLUE_OFF;
				}
				if(power_mode==MODE_OVERTEMP){
					RED_ON;GREEN_ON;BLUE_OFF;
				}
			}else{
				if(power_mode==MODE_OVERTEMP||power_mode==MODE_LOW_VOLTAGE){
					apply_led(0);
				}
			}

			// if((seconds%5==0) && ADMUX == 0b10000000){ //measure voltage in active mode
			if(adc_channel ==0 && d_seconds == 4){ //measure voltage in active mode
				if(val<LIMIT_9V){
					if(check_and_set_times(0)){
					  all_off();//completely discharged. turning off
					}
				}
				else if(power_mode!=MODE_OVERTEMP && power_mode!=MODE_LOW_VOLTAGE && power_mode>=MODE_IDLE){ //show voltage always, except overtemp
					if(val<((LIMIT_9V+LIMIT_10V)/2)){
						if(power_mode>=MODE_LOW && check_and_set_times(1)){ // усвловие нужно, чтобы не задалбывать функцию - в ней будут логи
							apply_led(0);
							power_mode = MODE_LOW_VOLTAGE;//low voltage
							apply_power();
						}
					}else if(val<LIMIT_10V){
						if(led_selected==0 || check_and_set_times(2) ){
							apply_led(1);
						}
						led_selected = 1;
					}else if(val<LIMIT_11V){
						if(led_selected==0 || check_and_set_times(3)){
							apply_led(2);
						}
						led_selected = 2;
					}else{
						if(led_selected==0 || check_and_set_times(4)){
							apply_led(3);
						}
						led_selected = 3;
					}
				}
			}
			while(d_seconds==4){}

			if(adc_channel ==1 && d_seconds == 8){ //measure temp in active mode
				if(val>330 && power_mode>=MODE_LOW && check_and_set_times(5)){// усвловие нужно, чтобы не задалбывать функцию - в ней будут логи
					power_mode = MODE_OVERTEMP;
					apply_power(); //overtemp. reduce current cunsumption
				}
			}
			while(d_seconds==8){}

			if(power_mode==MODE_IDLE && seconds>=7200){ //выключение через два часа из режима простоя
				all_off();
			}


			// if(seconds==0 && d_seconds<5 && power_mode>=MODE_LOW){
			// 	GIMSK = 0;//вырубим прерывания на первые 500мс, чтобы не кнопать кнопкой сильно часто
			// }else{
			// 	GIMSK = (1<<PCIE1);//interrupt on pin change0
			// }
		}
	}
}

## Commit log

2016-01-10 added ltspice simulation
2016-01-13 schematics roughly finished, components are roughly in place. Need accurate routing and fine component adjustments
2016-01-13 second iteration of component placement. already have routing improvements, but still plenty of work to do
2016-01-14 routing complete. main tasks to do: add polys, optimize routes width, add some extra vias, make gerbers
2016-01-14 added poly's & some traces optimization. Need to pretify silkscreen, check everything and make gerbers
2016-01-15 Added Gerbers and PartList
2016-01-15 Added BOM to readme
2016-01-16 Added calculations for XHP70
2016-01-20 added round version
2016-01-21 added vias for led in roud version, added second button pad in round version
2016-02-05 added 40mm version
2016-02-05 kevlin connection changed
2016-03-12 added rectifier and stab
2016-04-29 board routed and secondary protection removed
2016-05-04 mirrored charger board. this version has been ordered (charger&rect_and_stab)
2016-06-13 added adc resistors shutdown
2016-06-22 added resistor to adc
2016-07-18 firmware - added sleep mode and timer
2016-07-19 version 1.0
2016-07-25 moved components inside
2016-07-25 added eeprom storage, temporary disabled everything for testing
2016-07-25 added maximul stint calculation for eeprom stored data
2016-07-28 modified eeprom storage
2016-08-12 added ltc4012 version of charger
2016-09-04 restored accidentely commited low_voltage mode
2016-09-05 added 5 times check before switch
2016-09-05 release v 1.0
2017-08-07 Restores 32mm version

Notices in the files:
parts and their libraries:
SparkFun-DigitalIC: Licensing: Creative Commons ShareAlike 4.0 International - https://creativecommons.org/licenses/by-sa/4.0
